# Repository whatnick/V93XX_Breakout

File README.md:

# V93XX_Breakout
Breakouts for V93xx series single-phase energy monitors. Drivers for Arduino are available [here](https://github.com/whatnick/V93XX_Arduino).

## V9360 Breakout

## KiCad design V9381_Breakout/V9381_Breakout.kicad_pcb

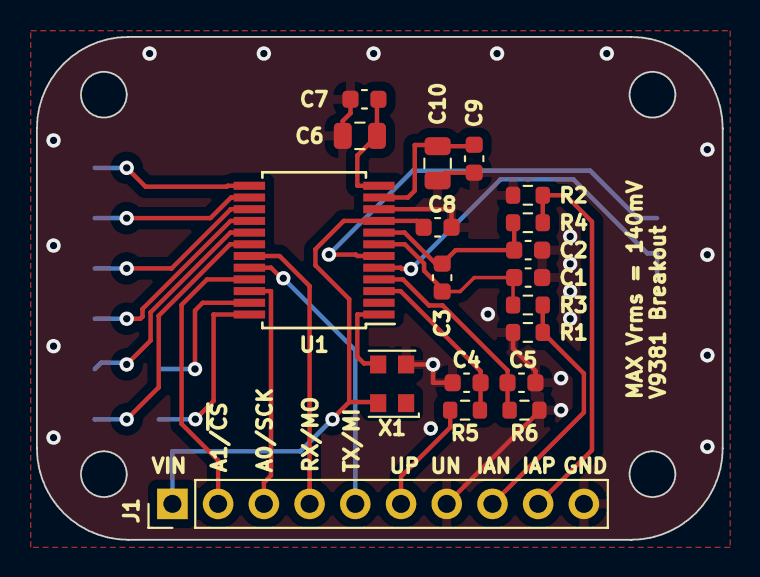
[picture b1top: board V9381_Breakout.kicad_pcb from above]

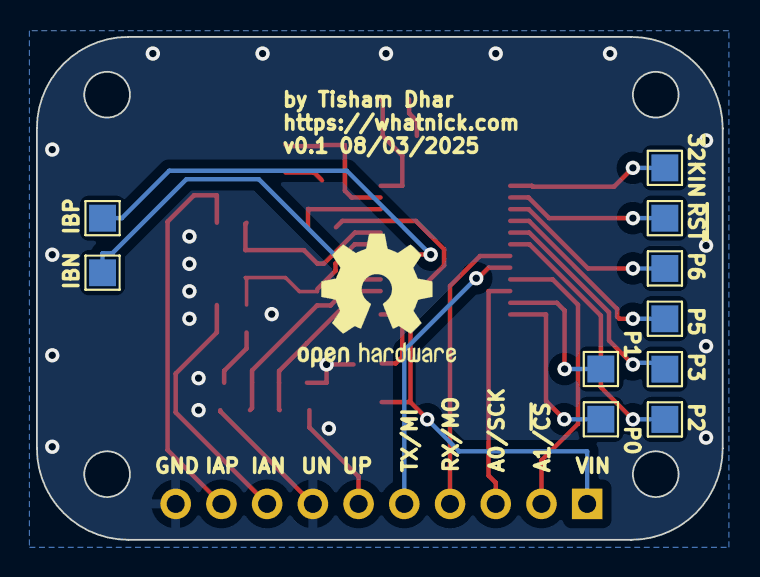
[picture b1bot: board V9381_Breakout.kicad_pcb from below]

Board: 2 copper layers, 38.1 x 27.9 mm, 30 parts (11 on the bottom side), 26 nets.

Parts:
C1, C2, C4, C5: 33n; C_0603_1608Metric
C3: 100p; C_0603_1608Metric
C6, C10: 4.7u; C_0805_2012Metric
C7, C8, C9: 100n; C_0603_1608Metric
J1: Conn_01x10; PinHeader_1x10_P2.54mm_Vertical
R1, R2: 2R2; R_0603_1608Metric
R3, R4, R5, R6: 1k; R_0603_1608Metric
SYM1: Logo_Open_Hardware_Small; OSHW-Logo2_9.8x8mm_SilkScreen
TP1, TP2, TP3, TP4, TP5, TP6, TP7, TP8, TP9, TP10: TestPoint; TestPoint_Pad_1.5x1.5mm
U1: V9381; SSOP-24_5.3x8.2mm_P0.65mm
X1: XO32; Oscillator_SMD_EuroQuartz_XO32-4Pin_3.2x2.5mm

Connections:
32KIN: TP10.1, U1.13 (32KIN)
CS: J1.2, U1.21 (A1/SPCSN)
GND: C1.2, C2.1, C4.2, C5.1, C6.1, C7.1, C8.2, C9.1, C10.1, J1.7, J1.10, R1.2, R2.1, R6.1, U1.10 (VSS), X1.2 (GND)
IAN: C1.1, C3.1, R3.2, U1.7 (IAN)
IAN_IN: J1.8, R1.1, R3.1
IAP: C2.2, C3.2, R4.2, U1.8 (IAP)
IAP_IN: J1.9, R2.2, R4.1
IBN: TP2.1, U1.5 (IBN)
IBP: TP1.1, U1.6 (IBP)
unnamed: U1.1 (CTI), X1.3 (OUT)
unnamed: C9.2, C10.2, U1.11 (DVCC)
unnamed: C6.2, C7.2, U1.12 (VREF)
P0: TP3.1, U1.24 (P0)
P1: TP4.1, U1.23 (P1)
P2: TP5.1, U1.18 (P2)
P3: TP6.1, U1.17 (P3)
P5: TP7.1, U1.16 (P5)
P6: TP8.1, U1.15 (P6)
RX/MOSI: J1.4, U1.19 (RX/MOSI)
SCK: J1.3, U1.22 (A0/SPCK)
TX/MISO: J1.5, U1.20 (TX/MISO)
UN: C5.2, R6.2, U1.4 (UN)
UP: C4.1, R5.2, U1.3 (UP)
UP_IN: J1.6, R5.1
VIN: C8.1, J1.1, U1.9 (VDD), X1.4 (V+)
~RST: TP9.1, U1.14 (RSTN)

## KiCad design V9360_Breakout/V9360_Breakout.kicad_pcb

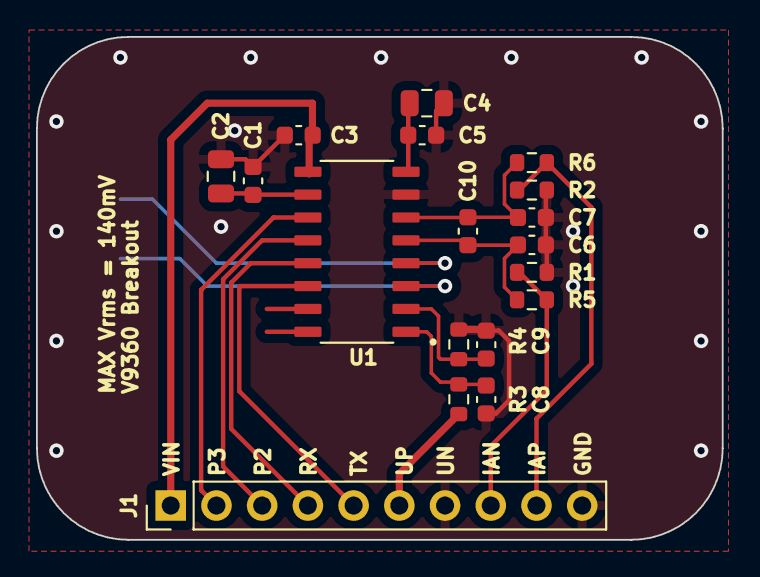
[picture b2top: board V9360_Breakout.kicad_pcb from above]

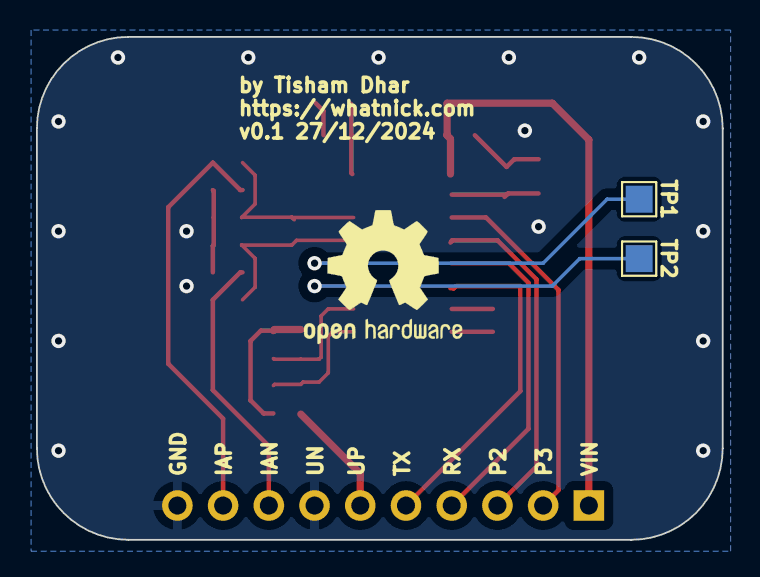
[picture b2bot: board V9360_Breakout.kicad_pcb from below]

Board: 2 copper layers, 38.1 x 27.9 mm, 21 parts (3 on the bottom side), 17 nets.

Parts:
C1, C3, C5: 100n; C_0603_1608Metric
C2, C4: 4.7u; C_0805_2012Metric
C6, C7, C8, C9: 33n; C_0603_1608Metric
C10: 100p; C_0603_1608Metric
J1: Conn_01x10_Pin; PinHeader_1x10_P2.54mm_Vertical
R1, R2: 2R2; R_0603_1608Metric
R3, R4, R5, R6: 1k; R_0603_1608Metric
SYM1: Logo_Open_Hardware_Small; OSHW-Logo2_9.8x8mm_SilkScreen
TP1, TP2: TestPoint; TestPoint_Pad_1.5x1.5mm
U1: V9360; SOP127P604X173-16N

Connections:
IAN: C6.1, C10.1, R5.2, U1.5 (IAN)
IAN_IN: J1.8, R1.1, R5.1
IAP: C7.2, C10.2, R6.2, U1.6 (IAP)
IAP_IN: J1.9, R2.2, R6.1
IBN: TP2.1, U1.3 (IBN)
IBP: TP1.1, U1.4 (IBP)
unnamed: C1.1, C2.1, U1.10 (DVCC)
unnamed: C4.2, C5.2, U1.8 (VREF)
P2: J1.3, U1.12 (P2)
P3: J1.2, U1.11 (P3)
RX: J1.4, U1.13 (RX)
TX: J1.5, U1.14 (TX)
UN: C9.2, R4.2, U1.2 (UN)
UN_IN: C1.2, C2.2, C3.2, C4.1, C5.1, C6.2, C7.1, C8.2, C9.1, J1.7, J1.10, R1.2, R2.1, R4.1, U1.7 (VSS)
UP: C8.1, R3.2, U1.1 (UP)
UP_IN: J1.6, R3.1
VIN: C3.1, J1.1, U1.9 (VDD)

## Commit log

2024-12-26 Initial symbol/footprint
2024-12-26 Convert to relative paths
2024-12-27 Add routing and filters
2024-12-27 Add silk screen refinements
2025-01-01 Add Gerbers and BOM
2025-02-23 Add docs
2025-03-04 Start creating V9381 Breakout
2025-03-06 Start the wiring up and PCB outline
2025-03-08 Finish routing
2025-03-08 Finish routing and create fab outputs
